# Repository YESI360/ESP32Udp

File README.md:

# ESP32Udp
Access Point
Server-multiClient
UDP Comunication server/client

# Link registro audiovisual de las versiones del sensor
(https://drive.google.com/drive/folders/1K7NjC36xgWDaGyBCJ0Mvloanyi_nB1H9?usp=sharing)

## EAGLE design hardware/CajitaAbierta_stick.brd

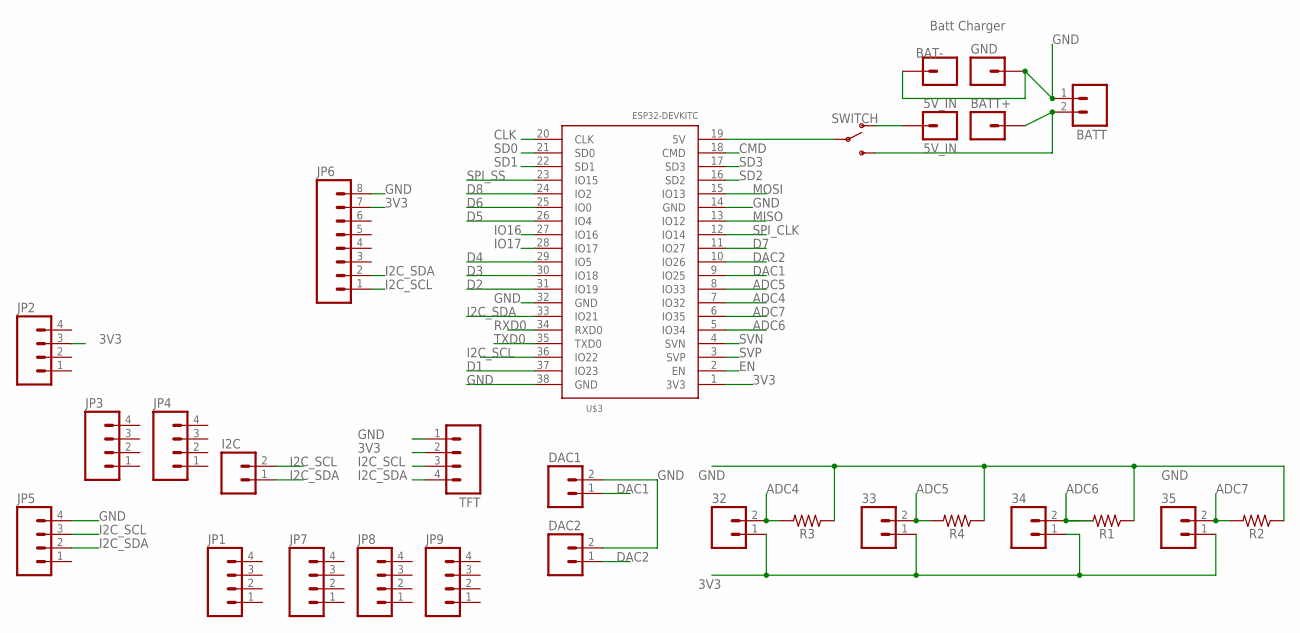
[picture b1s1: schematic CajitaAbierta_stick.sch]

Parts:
5V_IN: 5V_IN; 1X01
32, 33, 34, 35: M02PTH; 1X02
BAT-: M01PTH; 1X01
BATT: M02LOCK_LONGPADS; 1X02_LOCK_LONGPADS
BATT+: M01PTH; 1X01
DAC1, DAC2: M02PTH; 1X02
GND: Batt Charger; 1X01
I2C: M02PTH; 1X02
JP1, JP2, JP3, JP4, JP5, JP7, JP8, JP9: M04NO_SILK_ALL_ROUND; 1X04_NO_SILK_ALL_ROUND
JP6: M08; 1X08_ROUND
R1, R2, R3, R4: 1206
SWITCH: SWITCH-SPDT-SMD-RIGHT-ANGLE; SWITCH_SPST_SMD_A
TFT: M04PTH; 1X04
U$3: ESP32DEVKITC; ESP32-DEVKITC

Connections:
3V3: 32.1, 33.1, 34.1, 35.1, JP2.3, JP6.7, TFT.2, U$3.1 (3V3)
5V: SWITCH.2, U$3.19 (5V)
5V_IN: 5V_IN.1, SWITCH.1 (O)
ADC4: 32.2, R3.2, U$3.7 (IO32)
ADC5: 33.2, R4.2, U$3.8 (IO33)
ADC6: 34.2, R1.2, U$3.5 (IO34)
ADC7: 35.2, R2.2, U$3.6 (IO35)
BATT+: BATT.2, BATT+.1, SWITCH.3 (S)
CLK: U$3.20 (CLK)
CMD: U$3.18 (CMD)
D1: U$3.37 (IO23)
D2: U$3.31 (IO19)
D3: U$3.30 (IO18)
D4: U$3.29 (IO5)
D5: U$3.26 (IO4)
D6: U$3.25 (IO0)
D7: U$3.11 (IO27)
D8: U$3.24 (IO2)
DAC1: DAC1.1, U$3.9 (IO25)
DAC2: DAC2.1, U$3.10 (IO26)
EN: U$3.2 (EN)
GND: BAT-.1, BATT.1, DAC1.2, DAC2.2, GND.1, JP5.4, JP6.8, R1.1, R2.1, R3.1, R4.1, TFT.1, U$3.14 (GND), U$3.32 (GND), U$3.38 (GND)
I2C_SCL: I2C.2, JP5.3, JP6.1, TFT.3, U$3.36 (IO22)
I2C_SDA: I2C.1, JP5.2, JP6.2, TFT.4, U$3.33 (IO21)
IO16: U$3.27 (IO16)
IO17: U$3.28 (IO17)
MISO: U$3.13 (IO12)
MOSI: U$3.15 (IO13)
RXD0: U$3.34 (RXD0)
SD0: U$3.21 (SD0)
SD1: U$3.22 (SD1)
SD2: U$3.16 (SD2)
SD3: U$3.17 (SD3)
SPI_CLK: U$3.12 (IO14)
SPI_SS: U$3.23 (IO15)
SVN: U$3.4 (SVN)
SVP: U$3.3 (SVP)
TXD0: U$3.35 (TXD0)

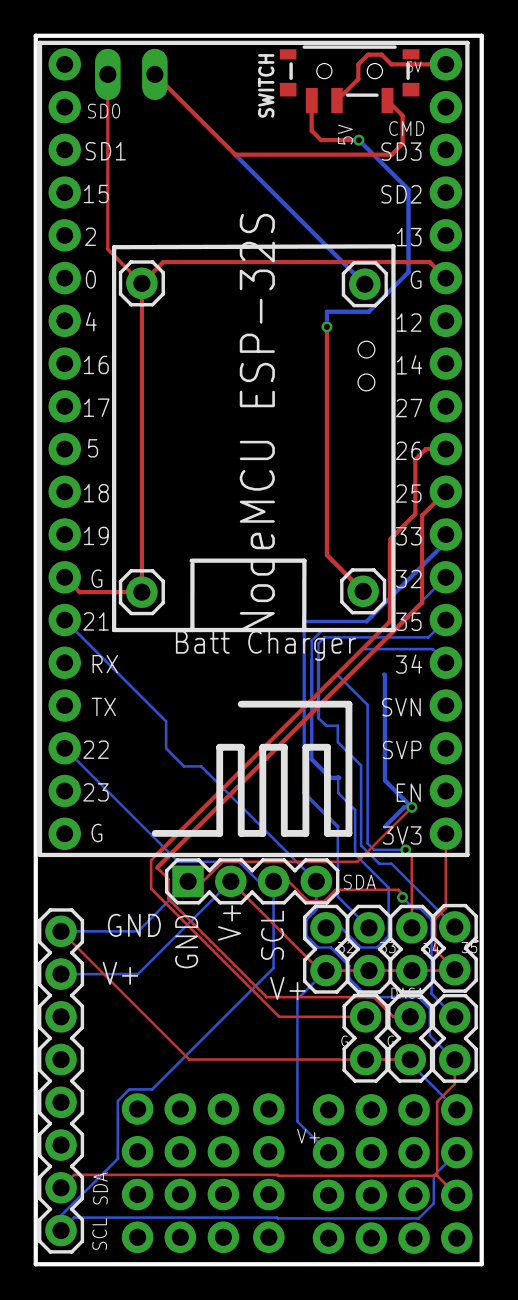
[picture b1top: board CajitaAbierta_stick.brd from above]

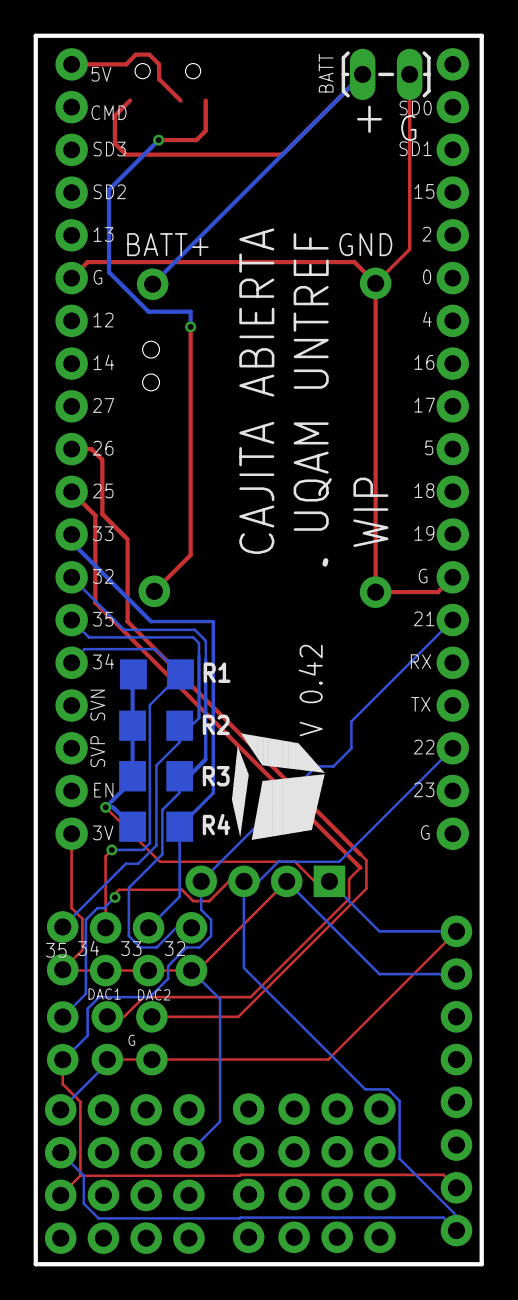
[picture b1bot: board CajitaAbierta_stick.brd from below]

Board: 2 copper layers, 26.5 x 73.0 mm, 28 parts (5 on the bottom side), 13 nets.

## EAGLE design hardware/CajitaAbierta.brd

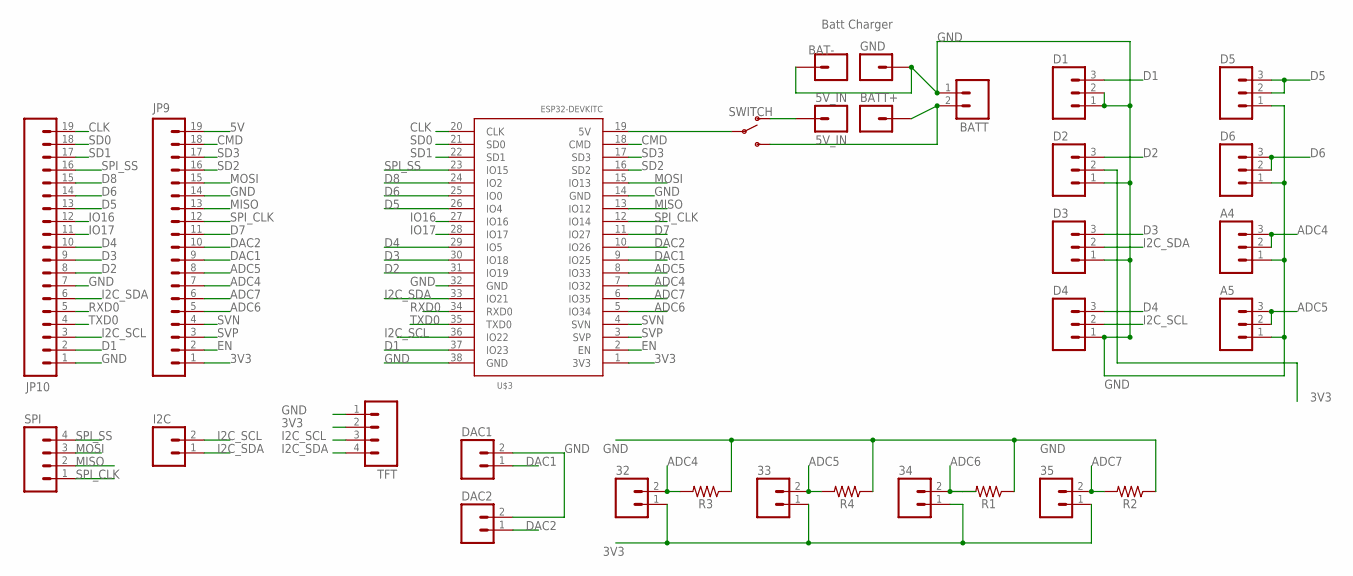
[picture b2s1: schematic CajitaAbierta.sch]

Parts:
5V_IN: 5V_IN; 1X01
32, 33, 34, 35: M02PTH; 1X02
A4, A5: M03LOCK_LONGPADS; 1X03_LOCK_LONGPADS
BAT-: M01PTH; 1X01
BATT: M02LOCK_LONGPADS; 1X02_LOCK_LONGPADS
BATT+: M01PTH; 1X01
D1, D2, D3, D4, D5, D6: M03LOCK_LONGPADS; 1X03_LOCK_LONGPADS
DAC1, DAC2: M02PTH; 1X02
GND: Batt Charger; 1X01
I2C: M02PTH; 1X02
JP9, JP10: M191X19; 1X19
R1, R2, R3, R4: 1206
SPI: M04PTH; 1X04
SWITCH: SWITCH-SPDT-SMD-RIGHT-ANGLE; SWITCH_SPST_SMD_A
TFT: M04PTH; 1X04
U$3: ESP32DEVKITC; ESP32-DEVKITC

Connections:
3V3: 32.1, 33.1, 34.1, 35.1, D2.2, JP9.1, TFT.2, U$3.1 (3V3)
5V: JP9.19, SWITCH.2, U$3.19 (5V)
5V_IN: 5V_IN.1, SWITCH.1 (O)
ADC4: 32.2, A4.2, A4.3, JP9.7, R3.2, U$3.7 (IO32)
ADC5: 33.2, A5.2, A5.3, JP9.8, R4.2, U$3.8 (IO33)
ADC6: 34.2, JP9.5, R1.2, U$3.5 (IO34)
ADC7: 35.2, JP9.6, R2.2, U$3.6 (IO35)
BATT+: BATT.2, BATT+.1, SWITCH.3 (S)
CLK: JP10.19, U$3.20 (CLK)
CMD: JP9.18, U$3.18 (CMD)
D1: D1.3, JP10.2, U$3.37 (IO23)
D2: D2.3, JP10.8, U$3.31 (IO19)
D3: D3.3, JP10.9, U$3.30 (IO18)
D4: D4.3, JP10.10, U$3.29 (IO5)
D5: D5.2, D5.3, JP10.13, U$3.26 (IO4)
D6: D6.2, D6.3, JP10.14, U$3.25 (IO0)
D7: JP9.11, U$3.11 (IO27)
D8: JP10.15, U$3.24 (IO2)
DAC1: DAC1.1, JP9.9, U$3.9 (IO25)
DAC2: DAC2.1, JP9.10, U$3.10 (IO26)
EN: JP9.2, U$3.2 (EN)
GND: A4.1, A5.1, BAT-.1, BATT.1, D1.1, D1.2, D2.1, D3.1, D4.1, D5.1, D6.1, DAC1.2, DAC2.2, GND.1, JP9.14, JP10.1, JP10.7, R1.1, R2.1, R3.1, R4.1, TFT.1, U$3.14 (GND), U$3.32 (GND), U$3.38 (GND)
I2C_SCL: D4.2, I2C.2, JP10.3, TFT.3, U$3.36 (IO22)
I2C_SDA: D3.2, I2C.1, JP10.6, TFT.4, U$3.33 (IO21)
IO16: JP10.12, U$3.27 (IO16)
IO17: JP10.11, U$3.28 (IO17)
MISO: JP9.13, SPI.2, U$3.13 (IO12)
MOSI: JP9.15, SPI.3, U$3.15 (IO13)
RXD0: JP10.5, U$3.34 (RXD0)
SD0: JP10.18, U$3.21 (SD0)
SD1: JP10.17, U$3.22 (SD1)
SD2: JP9.16, U$3.16 (SD2)
SD3: JP9.17, U$3.17 (SD3)
SPI_CLK: JP9.12, SPI.1, U$3.12 (IO14)
SPI_SS: JP10.16, SPI.4, U$3.23 (IO15)
SVN: JP9.4, U$3.4 (SVN)
SVP: JP9.3, U$3.3 (SVP)
TXD0: JP10.4, U$3.35 (TXD0)

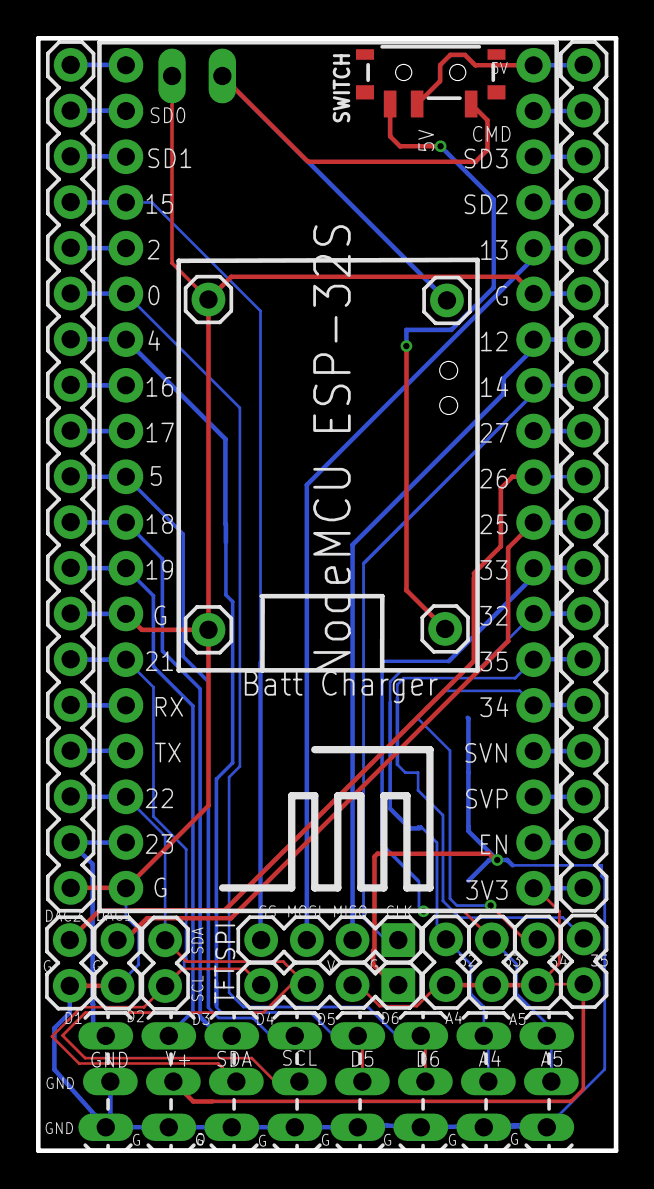
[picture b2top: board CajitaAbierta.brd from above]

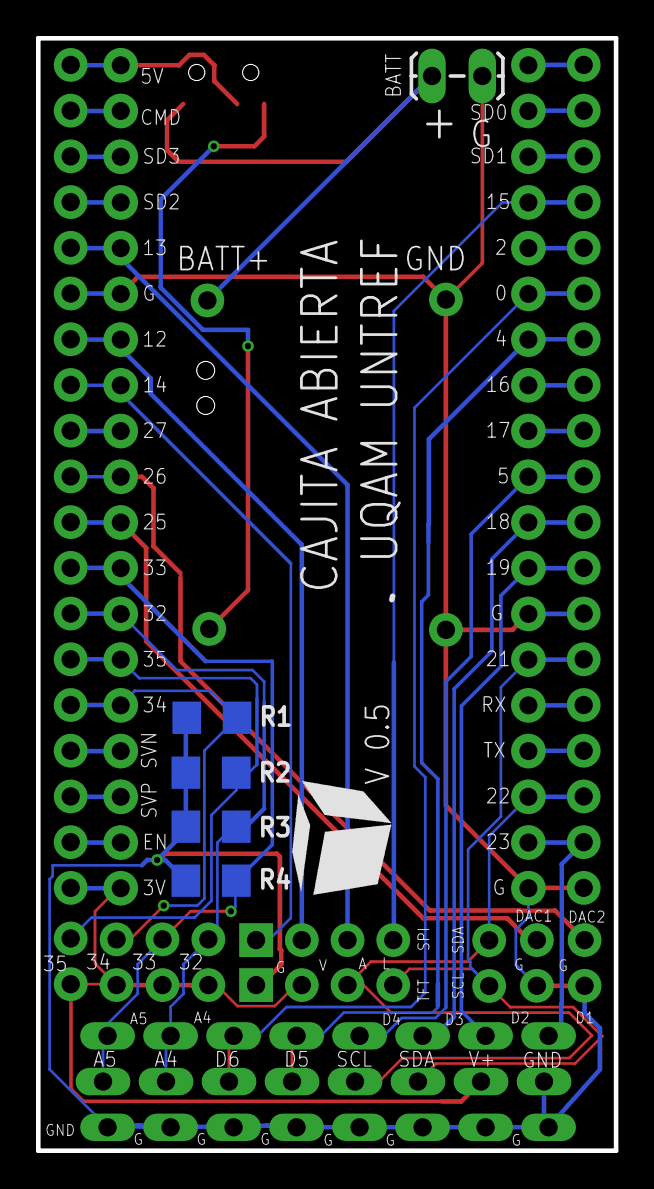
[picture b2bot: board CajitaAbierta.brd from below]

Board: 2 copper layers, 32.1 x 61.8 mm, 30 parts (5 on the bottom side), 38 nets.

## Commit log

2022-07-08 Create hardware

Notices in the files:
parts and their libraries:
SparkFun-Connectors: Licensing: Creative Commons ShareAlike 4.0 International - https://creativecommons.org/licenses/by-sa/4.0
